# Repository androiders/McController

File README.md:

# McController
Controller board for use with motorcycles in order to simplify electronic wiring. Something like the motogadget m unit but less advanced.

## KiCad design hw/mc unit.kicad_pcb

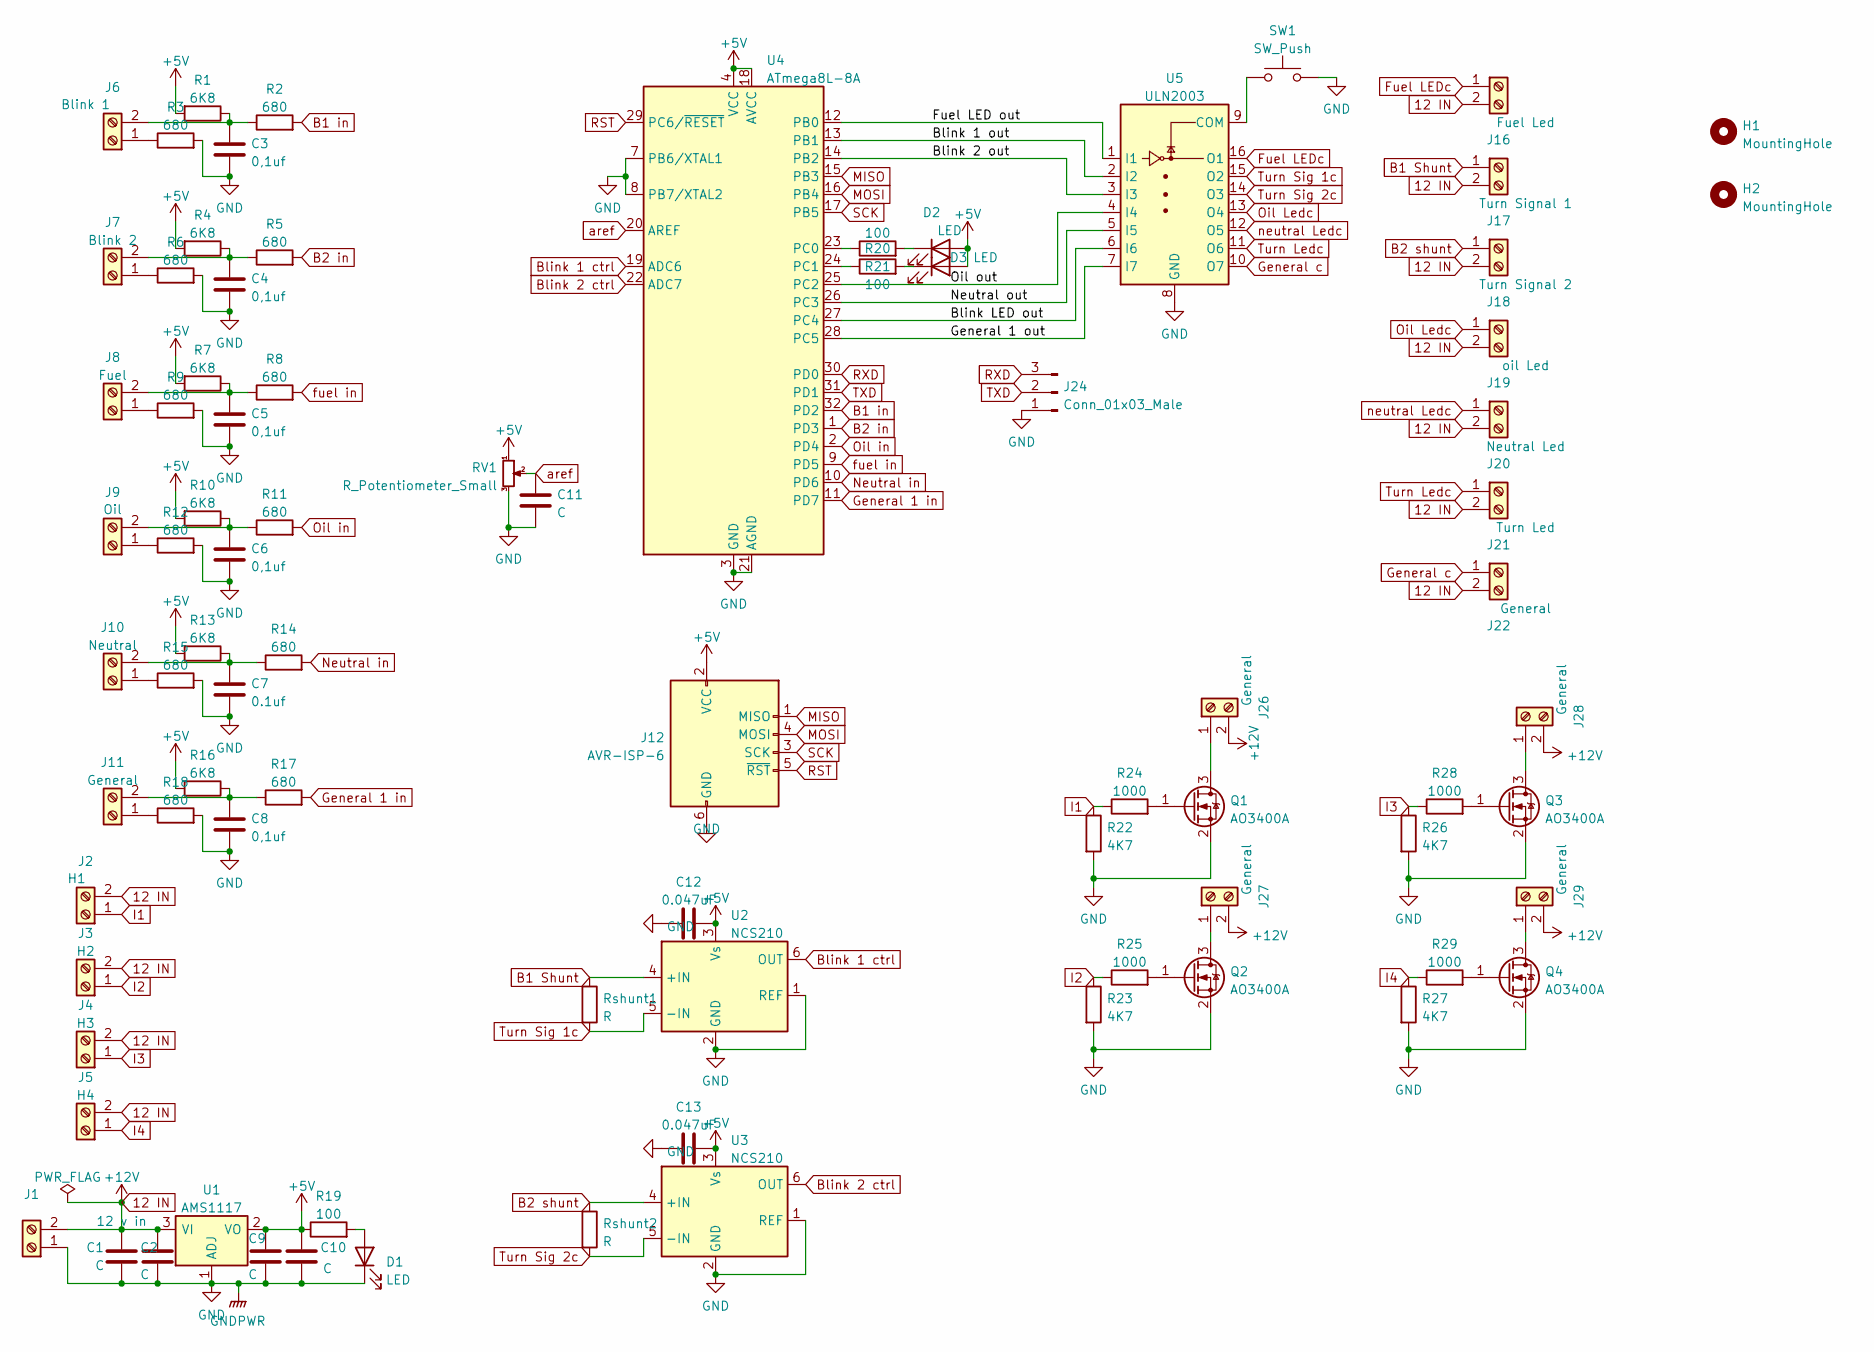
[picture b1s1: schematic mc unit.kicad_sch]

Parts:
C1, C2, C9, C10, C11: C; C_0805_2012Metric_Pad1.18x1.45mm_HandSolder
C3, C4, C5, C6, C8: 0,1uf; C_0805_2012Metric_Pad1.18x1.45mm_HandSolder
C7: 0.1uf; C_0805_2012Metric_Pad1.18x1.45mm_HandSolder
C12, C13: 0.047uF; C_0805_2012Metric_Pad1.18x1.45mm_HandSolder
D1, D2, D3: LED; LED_0805_2012Metric_Pad1.15x1.40mm_HandSolder
H1, H2: MountingHole; MountingHole_3.2mm_M3_DIN965
J1: 12 v in; TerminalBlock_Phoenix_MKDS-1,5-2-5.08_1x02_P5.08mm_Horizont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
J2: H1; TerminalBlock_TE_282834-2_1x02_P2.54mm_Horizontal
J3: H2; TerminalBlock_TE_282834-2_1x02_P2.54mm_Horizontal
J4: H3; TerminalBlock_TE_282834-2_1x02_P2.54mm_Horizontal
J5: H4; TerminalBlock_TE_282834-2_1x02_P2.54mm_Horizontal
J6: Blink 1; TerminalBlock_TE_282834-2_1x02_P2.54mm_Horizontal
J7: Blink 2; TerminalBlock_TE_282834-2_1x02_P2.54mm_Horizontal
J8: Fuel; TerminalBlock_TE_282834-2_1x02_P2.54mm_Horizontal
J9: Oil; TerminalBlock_TE_282834-2_1x02_P2.54mm_Horizontal
J10: Neutral; TerminalBlock_TE_282834-2_1x02_P2.54mm_Horizontal
J11, J22, J26, J27, J28, J29: General; TerminalBlock_TE_282834-2_1x02_P2.54mm_Horizontal
J12: AVR-ISP-6; IDC-Header_2x03_P2.54mm_Vertical
J16: Fuel Led; TerminalBlock_TE_282834-2_1x02_P2.54mm_Horizontal
J17: Turn Signal 1; TerminalBlock_TE_282834-2_1x02_P2.54mm_Horizontal
J18: Turn Signal 2; TerminalBlock_TE_282834-2_1x02_P2.54mm_Horizontal
J19: oil Led; TerminalBlock_TE_282834-2_1x02_P2.54mm_Horizontal
J20: Neutral Led; TerminalBlock_TE_282834-2_1x02_P2.54mm_Horizontal
J21: Turn Led; TerminalBlock_TE_282834-2_1x02_P2.54mm_Horizontal
J24: Conn_01x03_Male; PinHeader_1x03_P2.54mm_Vertical
Q1, Q2, Q3, Q4: AO3400A; SOT-23
R1, R4, R7, R10, R13, R16: 6K8; R_0603_1608Metric_Pad0.98x0.95mm_HandSolder
R2, R3, R5, R6, R8, R9, R11, R12, R14, R15, R17, R18: 680; R_0603_1608Metric_Pad0.98x0.95mm_HandSolder
R19, R20, R21: 100; R_0603_1608Metric_Pad0.98x0.95mm_HandSolder
R22, R23, R26, R27: 4K7; R_0805_2012Metric_Pad1.20x1.40mm_HandSolder
R24, R25, R28, R29: 1000; R_0805_2012Metric_Pad1.20x1.40mm_HandSolder
RV1: R_Potentiometer_Small; Potentiometer_Bourns_3266Y_Vertical
Rshunt1, Rshunt2: R; R_1206_3216Metric_Pad1.30x1.75mm_HandSolder
SW1: SW_Push; SW_SPST_CK_RS282G05A3
U1: AMS1117; SOT-223-3_TabPin2
U2, U3: NCS210; SOT-363_SC-70-6
U4: ATmega8L-8A; TQFP-32_7x7mm_P0.8mm
U5: ULN2003; SOIC-16_3.9x9.9mm_P1.27mm

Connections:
12 IN: C1.1, C2.1, J1.2, J2.2, J3.2, J4.2, J5.2, J16.2, J17.2, J18.2, J19.2, J20.2, J21.2, J22.2, J26.2, J27.2, J28.2, J29.2, U1.3 (VI)
+5V: C9.1, C10.1, C12.2, C13.2, D2.2 (A), D3.2 (A), J12.2 (VCC), R1.2, R4.2, R7.2, R10.2, R13.2, R16.2, R19.1, RV1.1, U1.2 (VO), U2.3 (Vs), U3.3 (Vs), U4.4 (VCC), U4.6 (VCC), U4.18 (AVCC)
/Blink 1 out: U4.13 (PB1), U5.2 (I2)
/Blink 2 out: U4.14 (PB2), U5.3 (I3)
/Blink LED out: U4.27 (PC4), U5.6 (I6)
/Fuel LED out: U4.12 (PB0), U5.1 (I1)
/General 1 out: U4.28 (PC5), U5.7 (I7)
/Neutral out: U4.26 (PC3), U5.5 (I5)
/Oil out: U4.25 (PC2), U5.4 (I4)
B1 Shunt: J17.1, Rshunt1.1, U2.4 (+IN)
B1 in: R2.2, U4.32 (PD2)
B2 in: R5.2, U4.1 (PD3)
B2 shunt: J18.1, Rshunt2.1, U3.4 (+IN)
Blink 1 ctrl: U2.6 (OUT), U4.19 (ADC6)
Blink 2 ctrl: U3.6 (OUT), U4.22 (ADC7)
Fuel LEDc: J16.1, U5.16 (O1)
GND: C1.2, C2.2, C3.2, C4.2, C5.2, C6.2, C7.2, C8.2, C9.2, C10.2, C11.2, C12.1, C13.1, D1.1 (K), J1.1, J12.6 (GND), J24.1, Q1.2 (S), Q2.2 (S), Q3.2 (S), Q4.2 (S), R3.2, R6.2, R9.2, R12.2, R15.2, R18.2, R22.2, R23.2, R26.2, R27.2, RV1.3, SW1.2, U1.1 (ADJ), U2.1 (REF), U2.2 (GND), U3.1 (REF), U3.2 (GND), U4.3 (GND), U4.5 (GND), U4.7 (PB6/XTAL1), U4.8 (PB7/XTAL2), U4.21 (AGND), U5.8 (GND)
General 1 in: R17.2, U4.11 (PD7)
General c: J22.1, U5.10 (O7)
I1: J2.1, R22.1, R24.1
I2: J3.1, R23.1, R25.1
I3: J4.1, R26.1, R28.1
I4: J5.1, R27.1, R29.1
MISO: J12.1 (MISO), U4.15 (PB3)
MOSI: J12.4 (MOSI), U4.16 (PB4)
unnamed: C3.1, J6.2, R1.1, R2.1
unnamed: C4.1, J7.2, R4.1, R5.1
unnamed: C5.1, J8.2, R7.1, R8.1
unnamed: C6.1, J9.2, R10.1, R11.1
unnamed: C7.1, J10.2, R13.1, R14.1
unnamed: C8.1, J11.2, R16.1, R17.1
unnamed: D1.2 (A), R19.2
unnamed: D2.1 (K), R20.2
unnamed: D3.1 (K), R21.2
unnamed: J6.1, R3.1
unnamed: J7.1, R6.1
unnamed: J8.1, R9.1
unnamed: J9.1, R12.1
unnamed: J10.1, R15.1
unnamed: J11.1, R18.1
unnamed: J27.1, Q2.3 (D)
unnamed: J29.1, Q4.3 (D)
unnamed: Q1.1 (G), R24.2
unnamed: J26.1, Q1.3 (D)
unnamed: Q2.1 (G), R25.2
unnamed: Q3.1 (G), R28.2
unnamed: J28.1, Q3.3 (D)
unnamed: Q4.1 (G), R29.2
unnamed: R20.1, U4.23 (PC0)
unnamed: R21.1, U4.24 (PC1)
unnamed: SW1.1, U5.9 (COM)
Neutral in: R14.2, U4.10 (PD6)
Oil Ledc: J19.1, U5.13 (O4)
Oil in: R11.2, U4.2 (PD4)
RST: J12.5 (~RST), U4.29 (PC6/~RESET)
RXD: J24.3, U4.30 (PD0)
SCK: J12.3 (SCK), U4.17 (PB5)
TXD: J24.2, U4.31 (PD1)
Turn Ledc: J21.1, U5.11 (O6)
Turn Sig 1c: Rshunt1.2, U2.5 (-IN), U5.15 (O2)
Turn Sig 2c: Rshunt2.2, U3.5 (-IN), U5.14 (O3)
aref: C11.1, RV1.2, U4.20 (AREF)
fuel in: R8.2, U4.9 (PD5)
neutral Ledc: J20.1, U5.12 (O5)

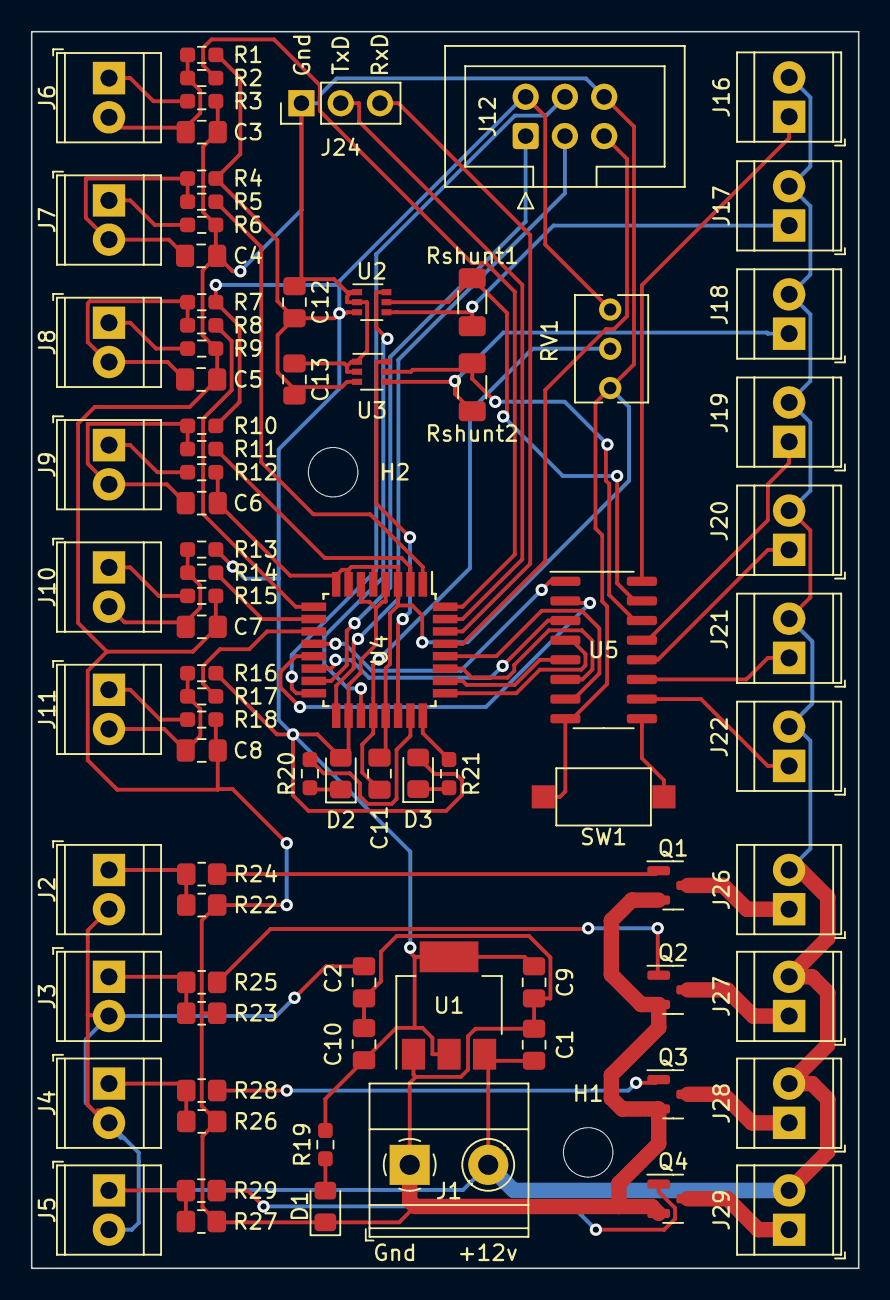
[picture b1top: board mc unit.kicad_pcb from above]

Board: 2 copper layers, 53.5 x 80.0 mm, 84 parts (0 on the bottom side), 64 nets.

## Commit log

2022-09-26 added hw files
2022-10-02 added sw shell
2022-10-06 updated to new version of this thingamabob
2022-10-06 added rendering just for fun :)
2022-10-06 enhancements!
